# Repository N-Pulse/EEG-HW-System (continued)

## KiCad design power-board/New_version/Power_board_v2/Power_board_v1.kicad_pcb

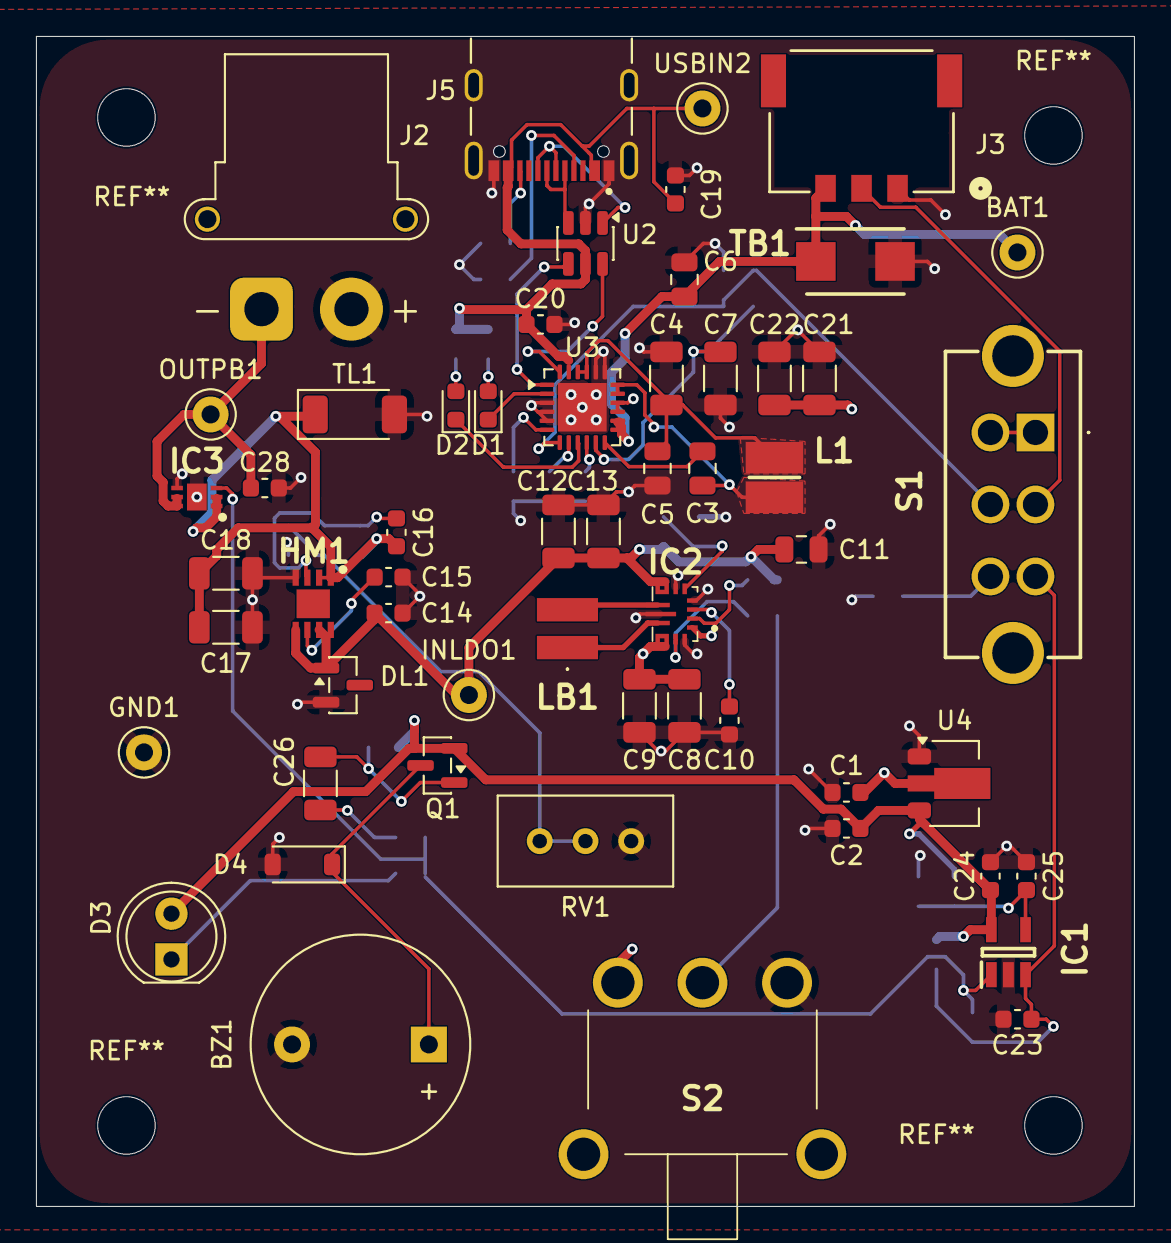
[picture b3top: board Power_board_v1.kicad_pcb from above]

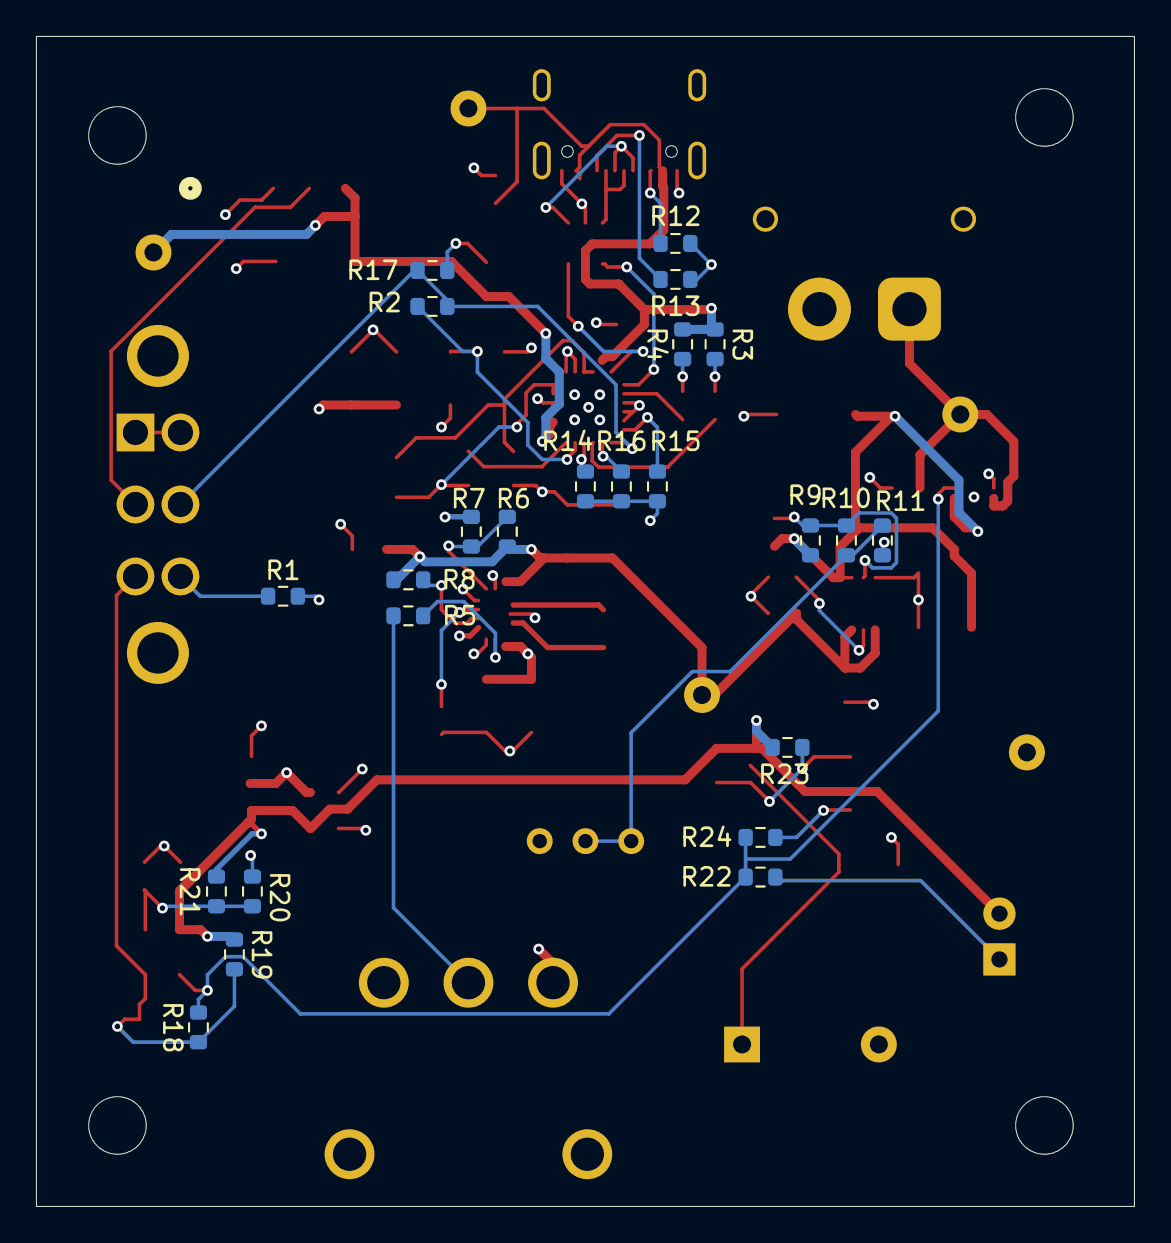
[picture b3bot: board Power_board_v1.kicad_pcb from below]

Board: 4 copper layers, 61.0 x 65.0 mm, 80 parts (24 on the bottom side), 46 nets.

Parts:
BAT1: TestPoint; TestPoint_Keystone_5000-5004_Miniature
BZ1: Buzzer; Buzzer_12x9.5RM7.6
C1, C2: 1uF; C_0603_1608Metric
C3: 47n; C_0805_2012Metric
C4, C21, C22: 22u; C_1206_3216Metric
C5, C6: 10u; C_0805_2012Metric
C7, C26: 4.7u; C_1206_3216Metric
C8, C9, C12, C13, C17, C18: 22uF; C_1206_3216Metric
C10, C14, C19, C23, C24, C25, C28: 100nF; C_0603_1608Metric
C11: 10uF; C_0805_2012Metric
C15: 220nF; C_0603_1608Metric
C16: 470nF; C_0603_1608Metric
C20: 1u; C_0603_1608Metric
D1, D2: LED_Small; LED_0603_1608Metric
D3: LED; LED_D5.0mm
D4: D; D_SOD-123
DL1: D_Zener; SOT-23
GND1: TestPoint; TestPoint_Keystone_5000-5004_Miniature
HM1: TPS7A8101DRBT; SON65P300X300X100-9N-D
IC1: MCP6541T-I_OT; SOT95P270X145-5N
IC2: TPS63070RNMR; TPS630701RNMR
IC3: AP2281-1FMG-7; SON50P201X181X60-7N
INLDO1: VinLDO; TestPoint_Keystone_5000-5004_Miniature
J2: XT30F; AMASS_XT30PW-F_1x02_P2.50mm_Horizontal
J3: 2053380003; CONN_2053380000-SD_03_MOL
J5: UJ20-C-H-G-SMT-1-P16-TR; SAMESKY_UJ20-C-H-G-SMT-1-P16-TR
L1: 1u; INDC3030X200N
LB1: 1.5uH; 78438336015
OUTPB1: VoutPB; TestPoint_Keystone_5000-5004_Miniature
Q1: BSS84; SOT-23
R1, R19, R20: 10k; R_0603_1608Metric
R2: 5.23k; R_0603_1608Metric
R3, R4, R24: 2.2k; R_0603_1608Metric
R5: 10kOhm; R_0603_1608Metric
R6: 665kOhm; R_0603_1608Metric
R7, R8: 100kOhm; R_0603_1608Metric
R9: 60.4k; R_0603_1608Metric
R10: 9.53k; R_0603_1608Metric
R11: 470; R_0603_1608Metric
R12, R13: 5.1k; R_0603_1608Metric
R14: 6.2k; R_0603_1608Metric
R15: 220k; R_0603_1608Metric
R16: 383; R_0603_1608Metric
R17: 30.1k; R_0603_1608Metric
R18: 51.1k; R_0603_1608Metric
R21: 26.7k; R_0603_1608Metric
R22: 330; R_0603_1608Metric
R23: 470k; R_0603_1608Metric
RV1: 0-500; Potentiometer_Bourns_3296W_Vertical
S1: MFS201N-9-Z; MFS201N9Z
S2: 5MS1S102AM6QES
TB1: D_Zener; DIOM5436X261N
TL1: D_SOD-128
U2: USBLC6-2SC6; SOT-23-6
U3: BQ25886RGE; Texas_RGE0024H_VQFN-24-1EP_4x4mm_P0.5mm_EP2.7x2.7mm
U4: MCP1703Ax-500xxMB; SOT-89-3
USBIN2: TestPoint; TestPoint_Keystone_5000-5004_Miniature

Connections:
/Buck 7.4 to 6.1V/EN: IC2.14 (EN), R5.2
/Buck 7.4 to 6.1V/FB: IC2.5 (FB), R6.2, R7.1
/Buck 7.4 to 6.1V/PG: IC2.2 (PG), R8.2
/Buck 7.4 to 6.1V/VAUX: C10.1, IC2.3 (VAUX)
/Buck 7.4 to 6.1V/VOUT BUCK BOOST: C11.1, C12.1, C13.1, C14.1, DL1.1 (K), HM1.5 (EN), HM1.7 (IN_1), HM1.8 (IN_2), IC2.7 (VOUT_1), IC2.8 (VOUT_2), IC2.17 (VOUT_1), INLDO1.1 (1_1), R6.1, R8.1
/Charging circuit/BTST: C3.2, U3.12 (BTST)
/Charging circuit/D+: U2.6 (I/O1), U3.24 (D+)
/Charging circuit/D-: U2.4 (I/O2), U3.1 (D-)
/Charging circuit/ICHGSET: R14.1, U3.10 (ICHGSET)
/Charging circuit/ILIM: R16.1, U3.8 (ILIM)
/Charging circuit/NTC: J3.2, S1.2 (COM_1)
/Charging circuit/PG: D2.1 (K), U3.9 (~PG)
/Charging circuit/PMID: C4.1, C5.1, L1.1, U3.21 (PMID), U3.22 (PMID)
/Charging circuit/REGN: C7.1, R2.1, U3.11 (REGN)
/Charging circuit/STAT: D1.1 (K), U3.2 (STAT)
/Charging circuit/SW: C3.1, L1.2, U3.17 (SW), U3.18 (SW)
/Charging circuit/SYS: C1.1, C8.1, C9.1, C21.1, C22.1, IC2.1 (PS/S), IC2.12 (VIN_1), IC2.13 (VIN_2), IC2.16 (VIN_1), S2.3 (NO), U3.15 (SYS), U3.16 (SYS), U4.2 (VI)
/Charging circuit/TS: R2.2, R17.1, S1.5 (COM_2), U3.7 (TS)
/Charging circuit/VBUS: C19.1, C20.1, J5.A4_B9 (VBUS), J5.B4_A9 (VBUS__1), R3.2, R4.2, U2.5 (VBUS), U3.23 (VBUS), USBIN2.1 (1_1)
/Charging circuit/VSET: R15.1, U3.6 (VSET)
/Temperature control/5V: C2.1, C24.1, D3.2 (A), IC1.5 (VDD), Q1.2 (S), R19.1, R21.1, R23.1, U4.3 (VO)
/Temperature control/INCOMP: C23.1, IC1.3 (VIN+), R18.1, R19.2, S1.3 (NC_1)
/Temperature control/OUT: IC1.1 (OUT), IC3.3 (EN), R18.2, R22.2, R24.2
BATTERY VOLTAGE: BAT1.1 (1_1), C6.1, J3.3, TB1.1 (K), U3.13 (BAT), U3.14 (BAT)
GND: BZ1.2 (-), C1.2, C2.2, C4.2, C5.2, C6.2, C7.2, C8.2, C9.2, C10.2, C11.2, C12.2, C13.2, C14.2, C15.2, C17.2, C18.2, C19.2, C20.2, C21.2, C22.2, C23.2, C24.2, C25.2, C28.2, D4.2 (A), DL1.2 (A), GND1.1 (1_1), HM1.4 (GND), IC1.2 (VSS), IC2.4 (GND), IC2.6 (FB2), IC2.10 (PGND), IC2.15 (VSEL), IC3.4 (GND_1), IC3.7 (GND_2), J2.2, J3.1, J5.A1_B12 (GND), J5.B1_A12 (GND__1), J5.SH1 (SHIELD), J5.SH2 (SHIELD__1), J5.SH3 (SHIELD__2), J5.SH4 (SHIELD__3), R1.2, R7.2, R11.2, R12.2, R13.2, R14.2, R15.2, R16.2, R17.2, R20.2, RV1.3, S2.1 (NC), TB1.2 (A), TL1.2 (A), U2.2 (GND), U3.3 (~CE), U3.4 (GND), U3.5 (OTG), U3.19 (GND), U3.20 (GND), U3.25 (GND), U4.1 (GND)
unnamed: BZ1.1 (+), D4.1 (K), Q1.3 (D)
unnamed: C26.2, R24.1
unnamed: D1.2 (A), R4.1
unnamed: D2.2 (A), R3.1
unnamed: D3.1 (K), R22.1
unnamed: C16.2, HM1.3 (FB/SNS), R9.2, R10.1
unnamed: C15.1, HM1.6 (NR)
unnamed: C16.1, C17.1, C18.1, HM1.1 (OUT_1), HM1.2 (OUT_2), IC3.1 (IN_1), IC3.2 (IN_2), R9.1, TL1.1 (K)
unnamed: C25.1, IC1.4 (VIN-), R20.1, R21.2
unnamed: IC2.11 (L1), LB1.1
unnamed: IC2.9 (L2), LB1.2
unnamed: J5.A5 (CC1), R13.1
unnamed: J5.B5 (CC2), R12.1
unnamed: J5.A7 (DN1), J5.B7 (DN2), U2.3 (I/O2)
unnamed: J5.A6 (DP1), J5.B6 (DP2), U2.1 (I/O1)
unnamed: C26.1, Q1.1 (G), R23.2
unnamed: R10.2, R11.1, RV1.1, RV1.2
unnamed: R1.1, S1.6 (NC_2)
unnamed: S1.1 (NO_1), S1.4 (NO_2)
unnamed: R5.1, S2.2 (COM)
VOUT PB: C28.1, IC3.5 (OUT_1), IC3.6 (OUT_2), J2.1, OUTPB1.1 (1_1)
